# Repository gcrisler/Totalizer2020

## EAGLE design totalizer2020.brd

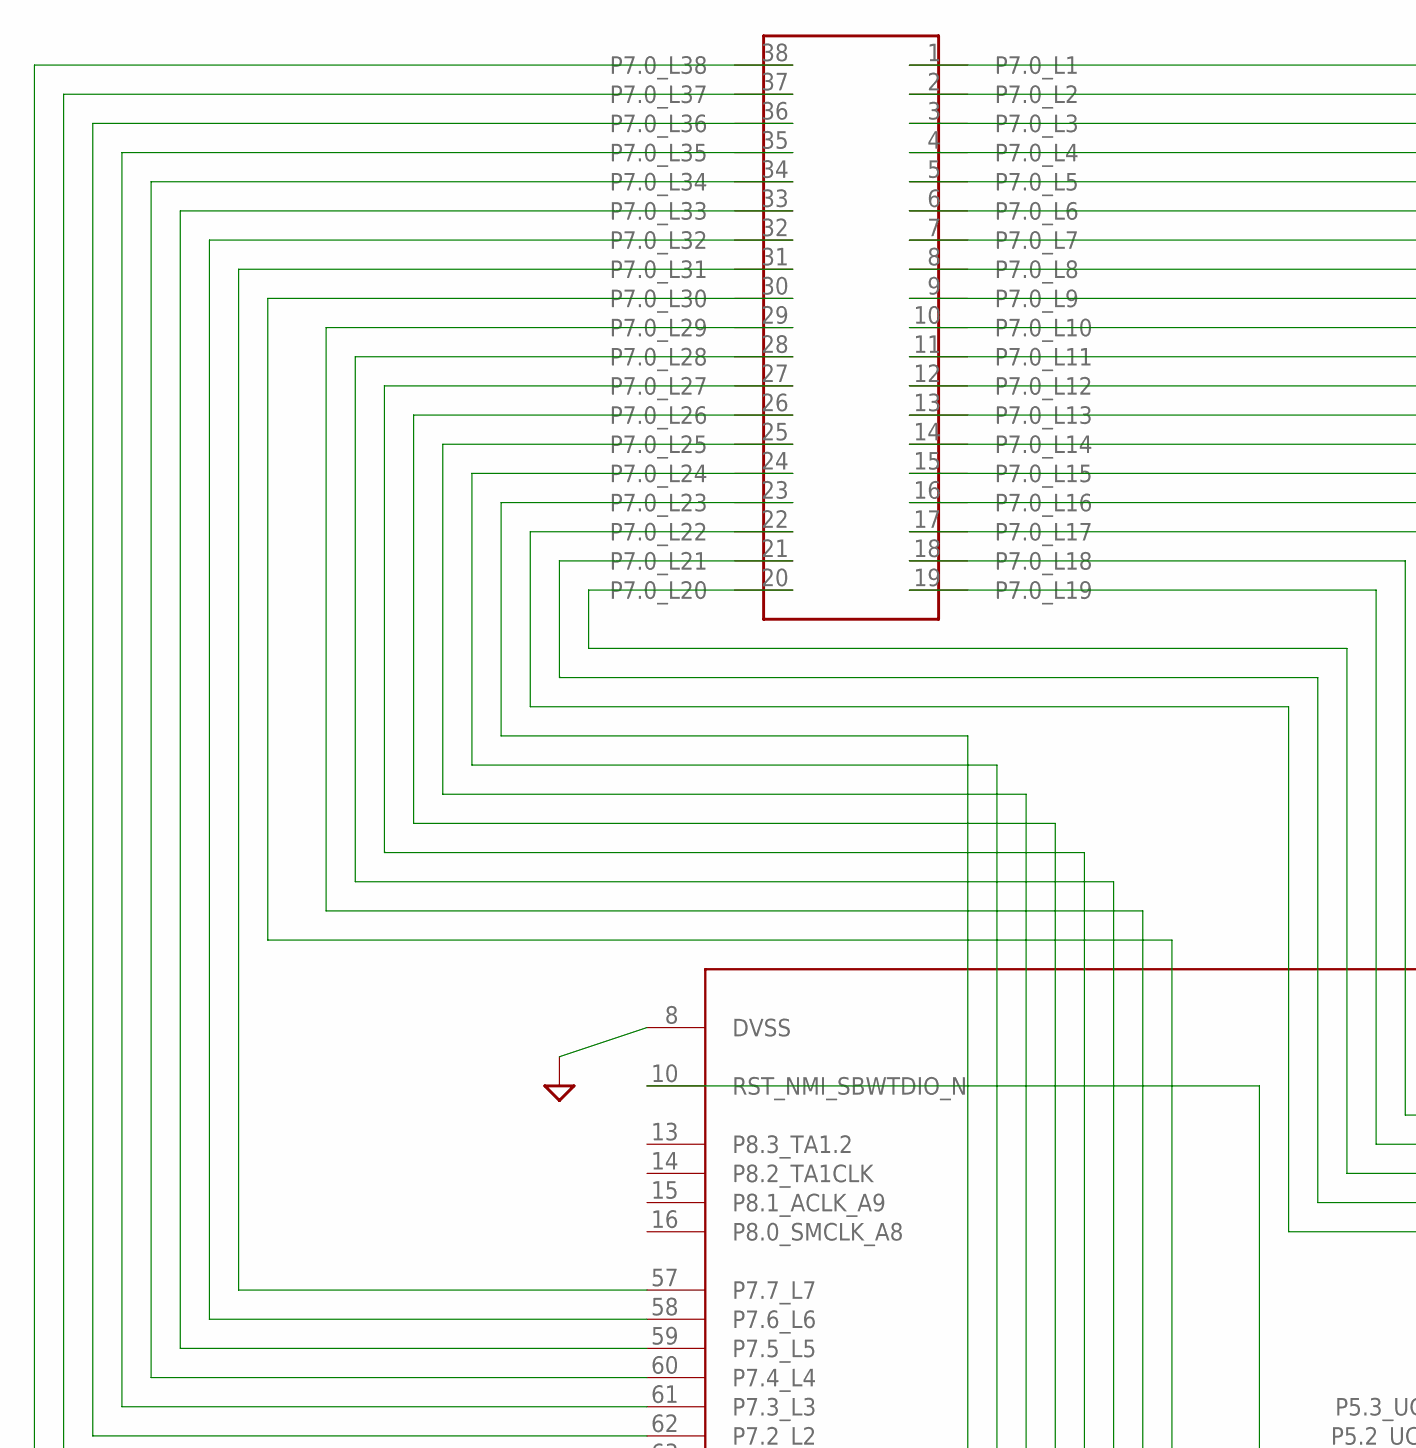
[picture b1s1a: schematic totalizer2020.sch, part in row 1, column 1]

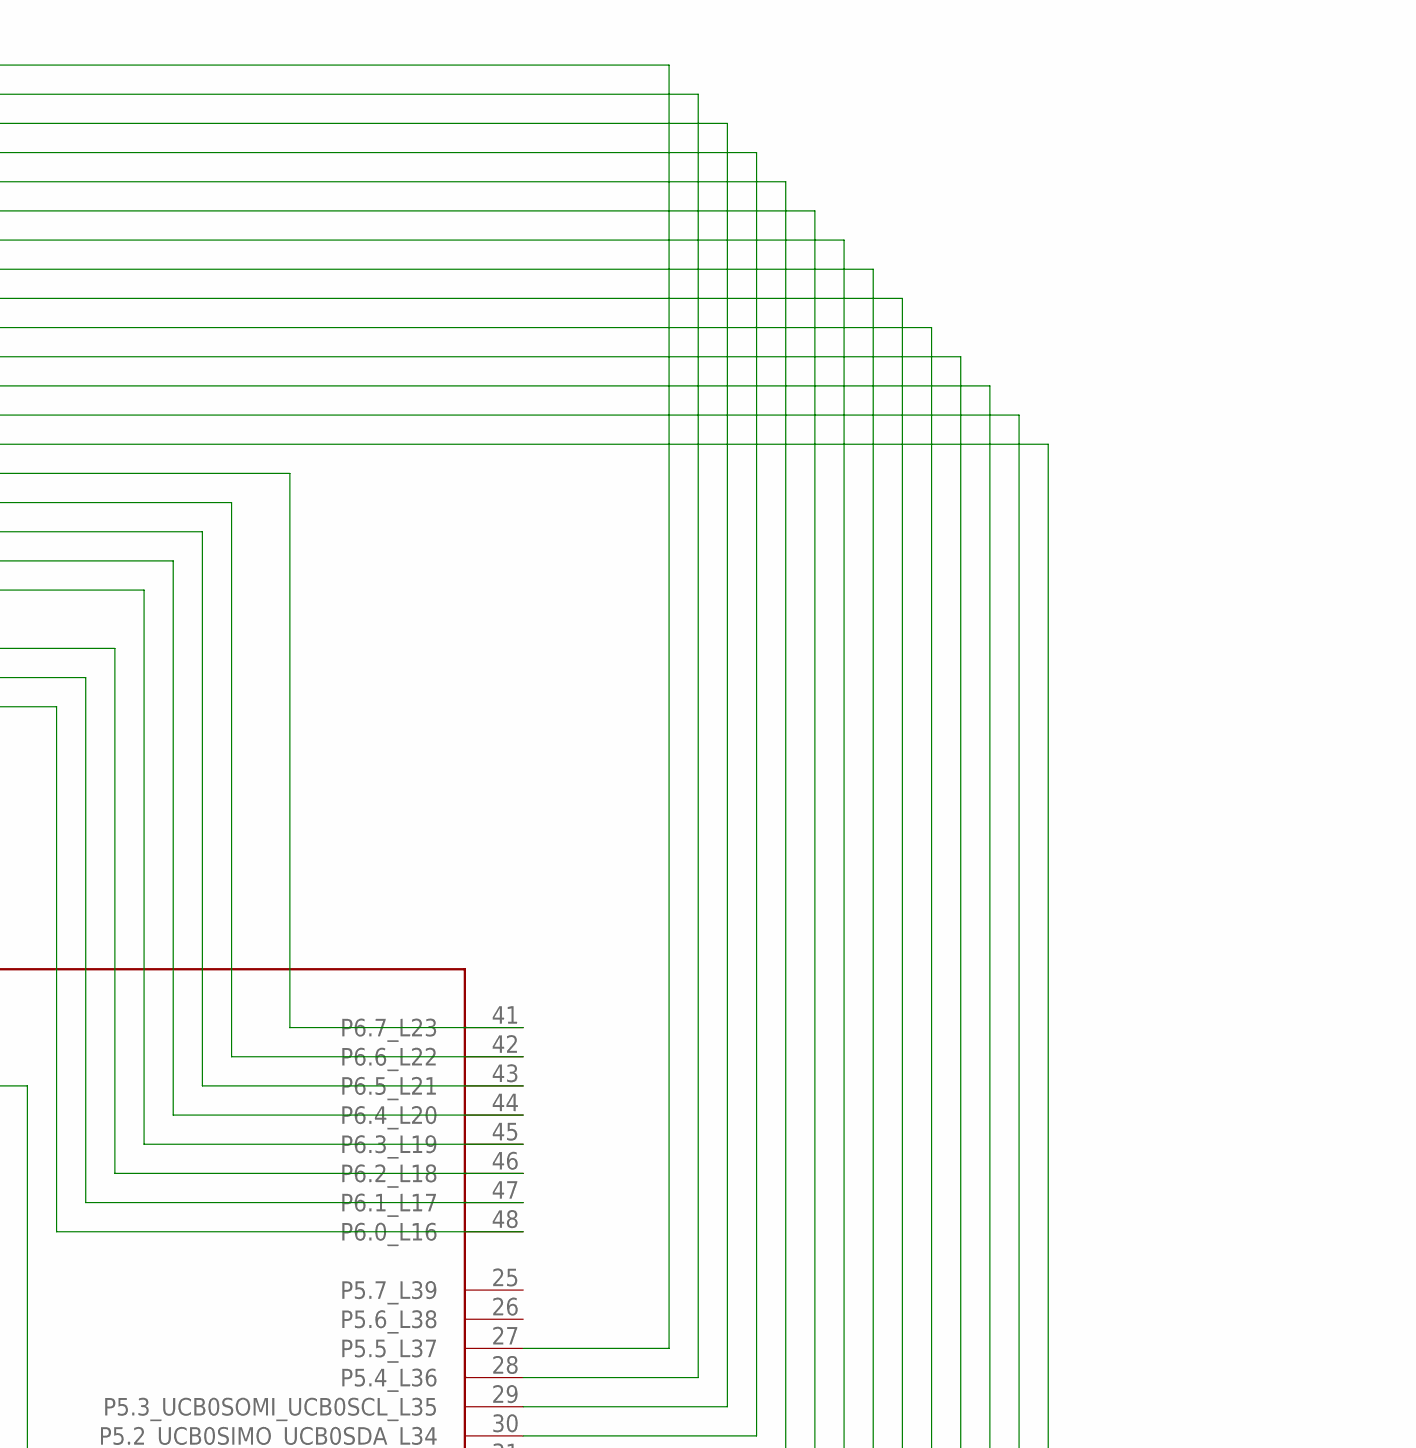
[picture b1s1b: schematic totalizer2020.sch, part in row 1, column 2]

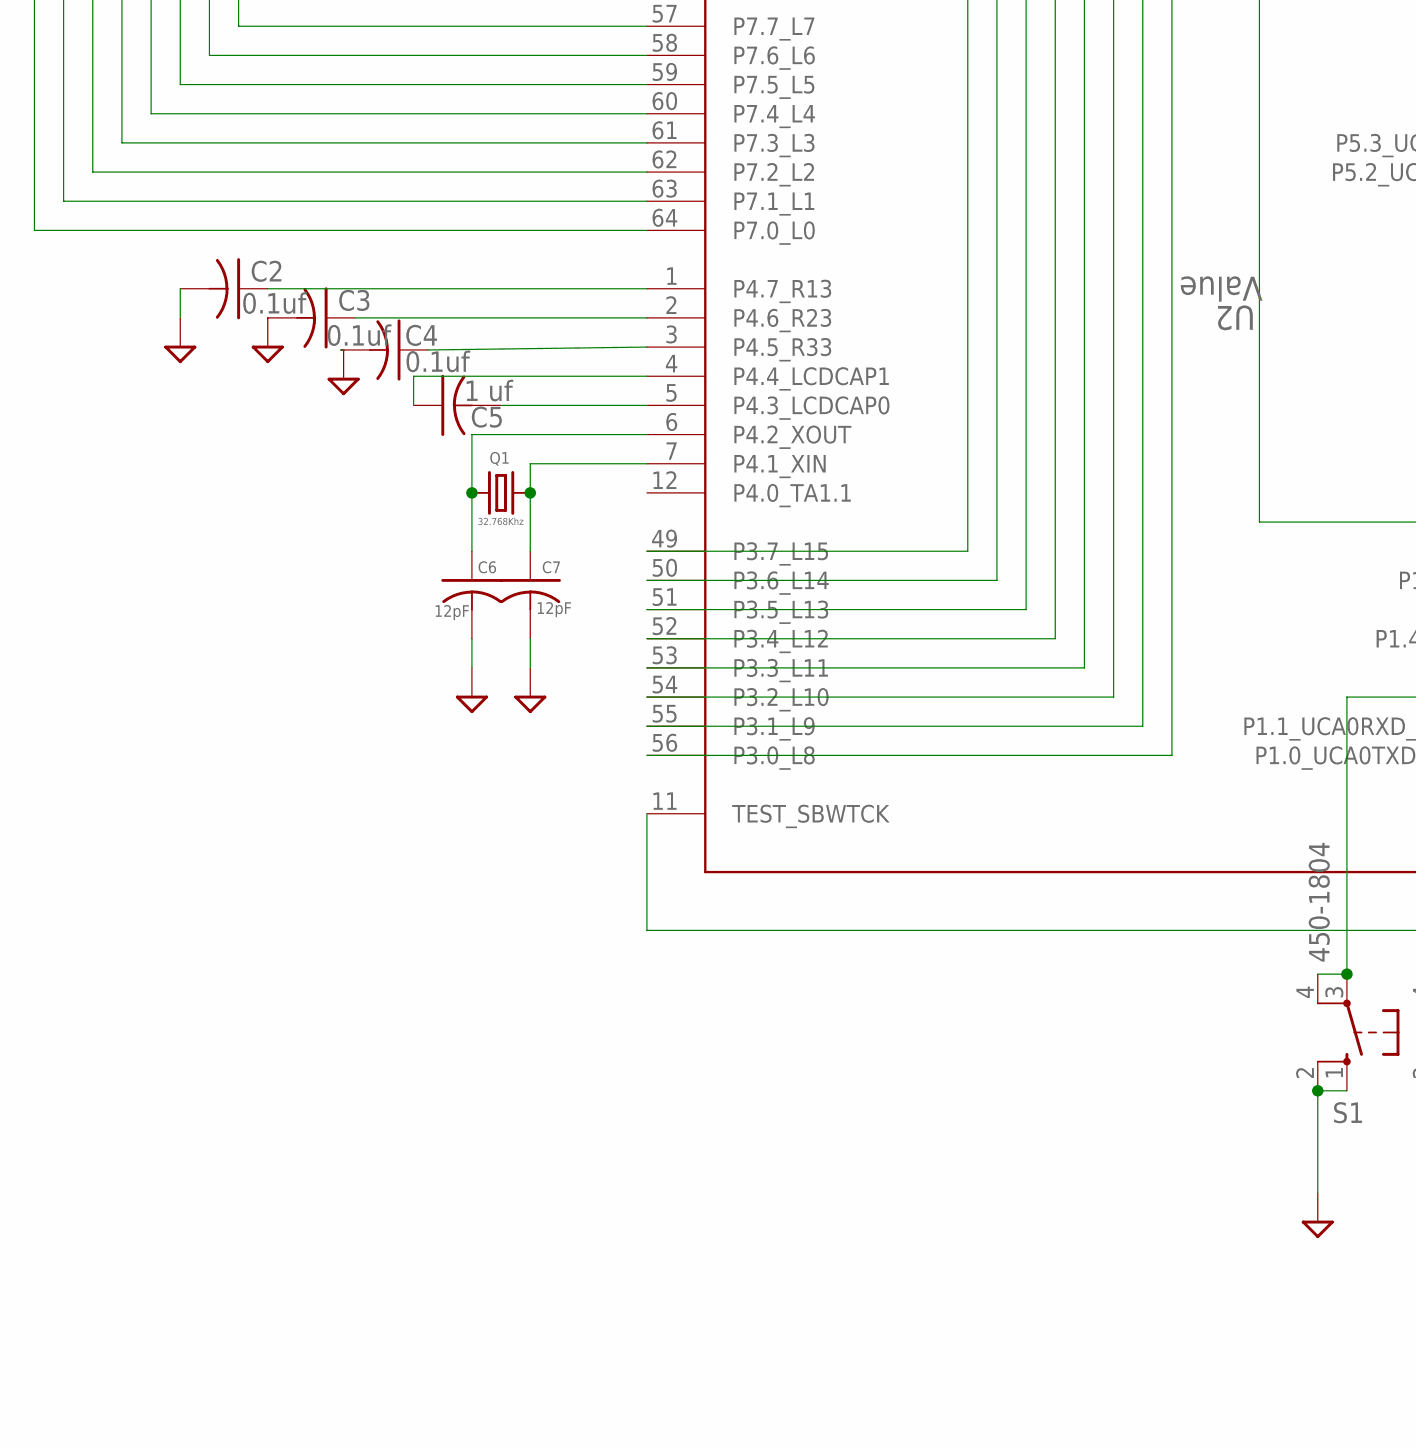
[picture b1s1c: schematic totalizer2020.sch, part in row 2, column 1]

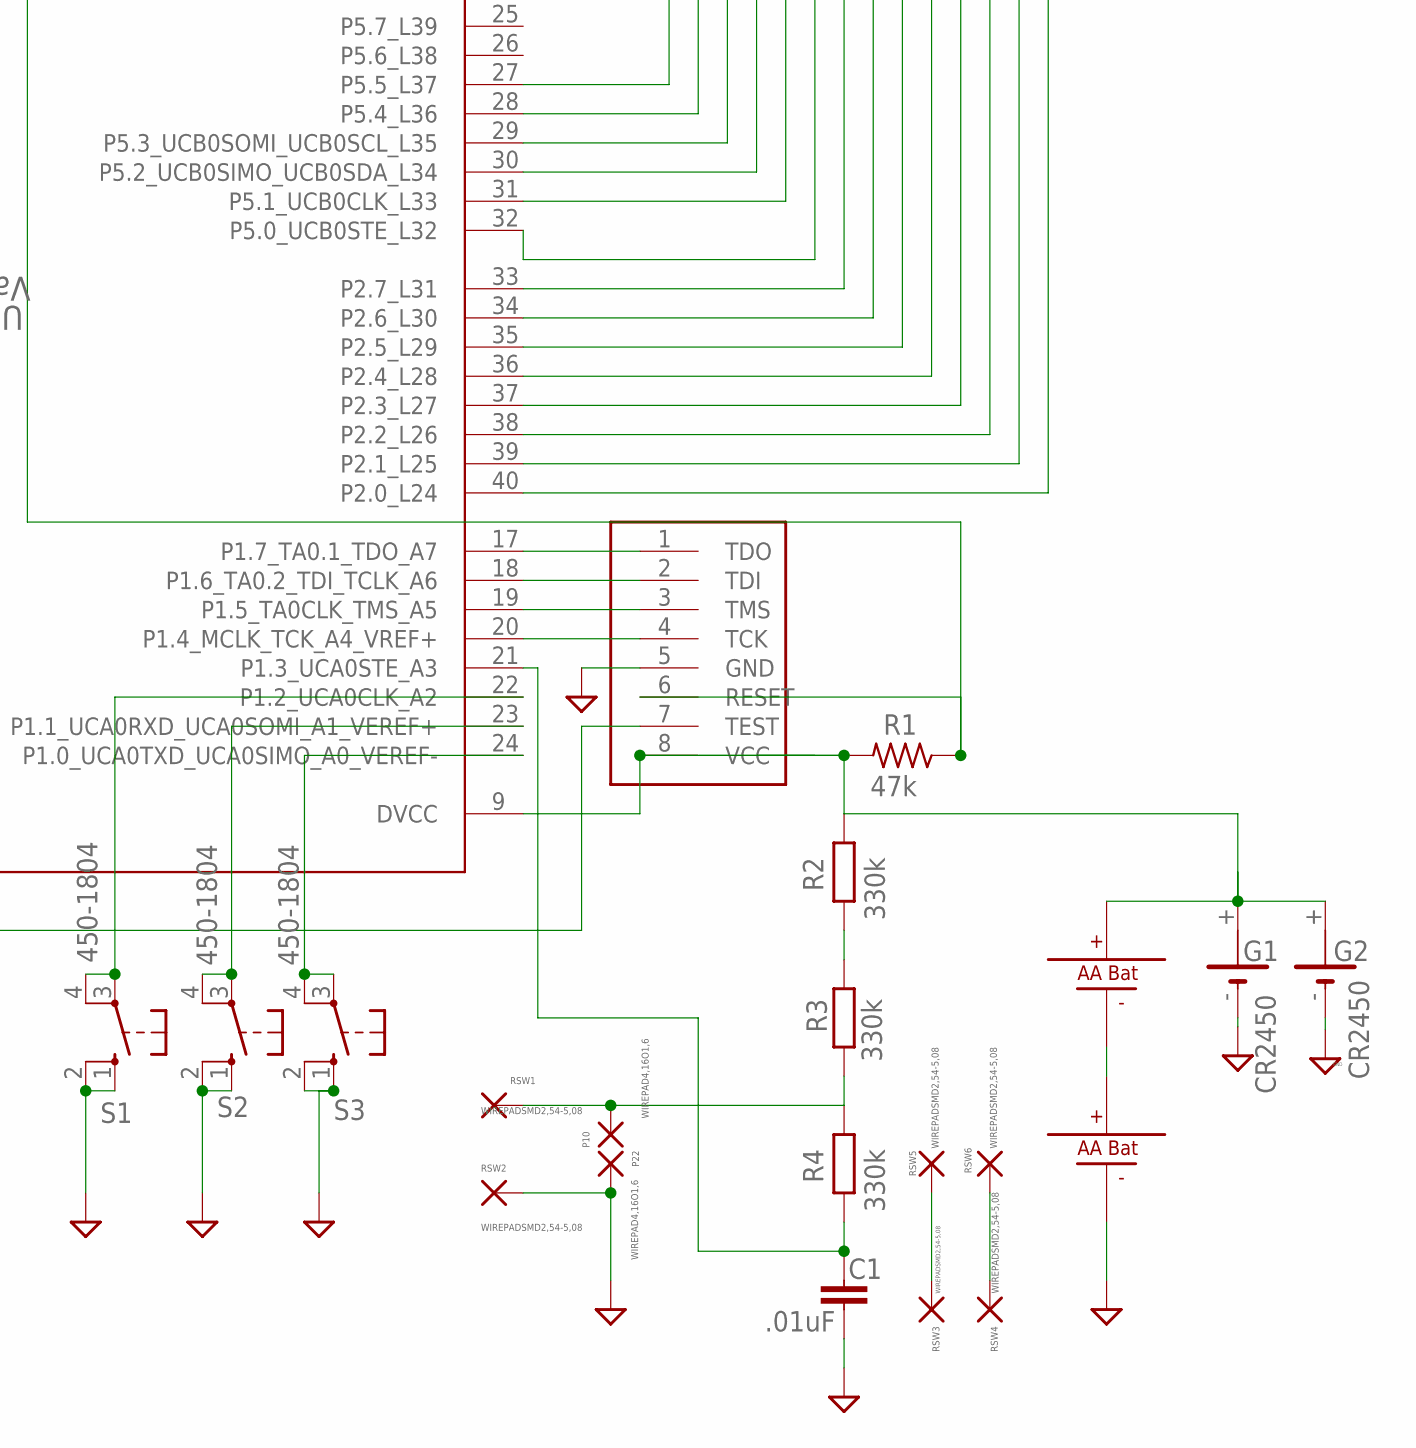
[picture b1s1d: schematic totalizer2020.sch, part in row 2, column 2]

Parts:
8PINCONNECTOR: JST-8JST-8; HDRVR8W64P150_1X8_1200X350X500B
C1: .01uF; C0805
C2, C3, C4: 0.1uf; C0805
C5: 1 uf; C0805
C6, C7: 12pF; C0805
G1, G2: CR2450; CR2430H
P10, P22: WIREPAD4,16O1,6; 4,16O1,6
Q1: 32.768Khz; 3.2X1.5
R1: 47k; R0805
R2, R3, R4: 330k; R0805
RSW1, RSW2, RSW3, RSW4, RSW5, RSW6: WIREPADSMD2,54-5,08; SMD2,54-5,08
S1, S2, S3: 450-1804; B3F-10XX
U2: Value; PM0064A_N
U$1: LCD-38LCD-38; DIP7140W53P200L5505H450Q38B
U$2, U$3: AA_BATTERY

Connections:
GND: 8PINCONNECTOR.5 (GND), C1.1, C2.2, C3.2, C4.2, C6.2, C7.2, G1.-, G2.-, P22.1, RSW2.1, S1.1 (S), S1.2 (S1), S2.1 (S), S2.2 (S1), S3.1 (S), S3.2 (S1), U2.8 (DVSS), U$3.3 (BAT_-), U$3.4 (BAT_-)
unnamed: 8PINCONNECTOR.1 (TDO), U2.17 (P1.7_TA0.1_TDO_A7)
unnamed: 8PINCONNECTOR.2 (TDI), U2.18 (P1.6_TA0.2_TDI_TCLK_A6)
unnamed: 8PINCONNECTOR.3 (TMS), U2.19 (P1.5_TA0CLK_TMS_A5)
unnamed: 8PINCONNECTOR.4 (TCK), U2.20 (P1.4_MCLK_TCK_A4_VREF+)
unnamed: C6.1, Q1.1, U2.6 (P4.2_XOUT)
unnamed: 8PINCONNECTOR.6 (RESET), R1.1, U2.10 (RST_NMI_SBWTDIO_N)
unnamed: 8PINCONNECTOR.7 (TEST), U2.11 (TEST_SBWTCK)
unnamed: RSW3.1, RSW5.1
unnamed: S2.3, S2.4 (P1), U2.23 (P1.1_UCA0RXD_UCA0SOMI_A1_VEREF+)
unnamed: S1.3, S1.4 (P1), U2.22 (P1.2_UCA0CLK_A2)
unnamed: C5.1, U2.4 (P4.4_LCDCAP1)
unnamed: S3.3, S3.4 (P1), U2.24 (P1.0_UCA0TXD_UCA0SIMO_A0_VEREF-)
unnamed: C5.2, U2.5 (P4.3_LCDCAP0)
unnamed: C4.1, U2.3 (P4.5_R33)
unnamed: C3.1, U2.2 (P4.6_R23)
unnamed: C2.1, U2.1 (P4.7_R13)
unnamed: 8PINCONNECTOR.8 (VCC), G1.+, G2.+, R1.2, R2.1, U2.9 (DVCC), U$2.2 (BAT_+), U$2.P1 (BAT_+)
unnamed: C1.2, R4.2, U2.21 (P1.3_UCA0STE_A3)
unnamed: C7.1, Q1.2, U2.7 (P4.1_XIN)
unnamed: U2.64 (P7.0_L0), U$1.38 (P7.0_L38)
unnamed: U2.63 (P7.1_L1), U$1.37 (P7.0_L37)
unnamed: U2.62 (P7.2_L2), U$1.36 (P7.0_L36)
unnamed: U2.61 (P7.3_L3), U$1.35 (P7.0_L35)
unnamed: U2.60 (P7.4_L4), U$1.34 (P7.0_L34)
unnamed: U2.59 (P7.5_L5), U$1.33 (P7.0_L33)
unnamed: U2.58 (P7.6_L6), U$1.32 (P7.0_L32)
unnamed: U2.57 (P7.7_L7), U$1.31 (P7.0_L31)
unnamed: U2.56 (P3.0_L8), U$1.30 (P7.0_L30)
unnamed: U2.55 (P3.1_L9), U$1.29 (P7.0_L29)
unnamed: U2.54 (P3.2_L10), U$1.28 (P7.0_L28)
unnamed: U2.53 (P3.3_L11), U$1.27 (P7.0_L27)
unnamed: U2.52 (P3.4_L12), U$1.26 (P7.0_L26)
unnamed: U2.51 (P3.5_L13), U$1.25 (P7.0_L25)
unnamed: U2.50 (P3.6_L14), U$1.24 (P7.0_L24)
unnamed: U2.49 (P3.7_L15), U$1.23 (P7.0_L23)
unnamed: U2.48 (P6.0_L16), U$1.22 (P7.0_L22)
unnamed: U2.47 (P6.1_L17), U$1.21 (P7.0_L21)
unnamed: U2.46 (P6.2_L18), U$1.20 (P7.0_L20)
unnamed: U2.45 (P6.3_L19), U$1.19 (P7.0_L19)
unnamed: U2.44 (P6.4_L20), U$1.18 (P7.0_L18)
unnamed: U$2.3 (BAT_-), U$2.4 (BAT_-), U$3.2 (BAT_+), U$3.P1 (BAT_+)
unnamed: U2.43 (P6.5_L21), U$1.17 (P7.0_L17)
unnamed: U2.42 (P6.6_L22), U$1.16 (P7.0_L16)
unnamed: U2.41 (P6.7_L23), U$1.15 (P7.0_L15)
unnamed: U2.40 (P2.0_L24), U$1.14 (P7.0_L14)
unnamed: U2.39 (P2.1_L25), U$1.13 (P7.0_L13)
unnamed: U2.38 (P2.2_L26), U$1.12 (P7.0_L12)
unnamed: U2.37 (P2.3_L27), U$1.11 (P7.0_L11)
unnamed: U2.36 (P2.4_L28), U$1.10 (P7.0_L10)
unnamed: U2.35 (P2.5_L29), U$1.9 (P7.0_L9)
unnamed: U2.34 (P2.6_L30), U$1.8 (P7.0_L8)
unnamed: U2.33 (P2.7_L31), U$1.7 (P7.0_L7)
unnamed: U2.32 (P5.0_UCB0STE_L32), U$1.6 (P7.0_L6)
unnamed: U2.31 (P5.1_UCB0CLK_L33), U$1.5 (P7.0_L5)
unnamed: U2.30 (P5.2_UCB0SIMO_UCB0SDA_L34), U$1.4 (P7.0_L4)
unnamed: U2.29 (P5.3_UCB0SOMI_UCB0SCL_L35), U$1.3 (P7.0_L3)
unnamed: U2.28 (P5.4_L36), U$1.2 (P7.0_L2)
unnamed: U2.27 (P5.5_L37), U$1.1 (P7.0_L1)
unnamed: RSW4.1, RSW6.1
unnamed: R2.2, R3.2
unnamed: P10.1, R3.1, R4.1, RSW1.1

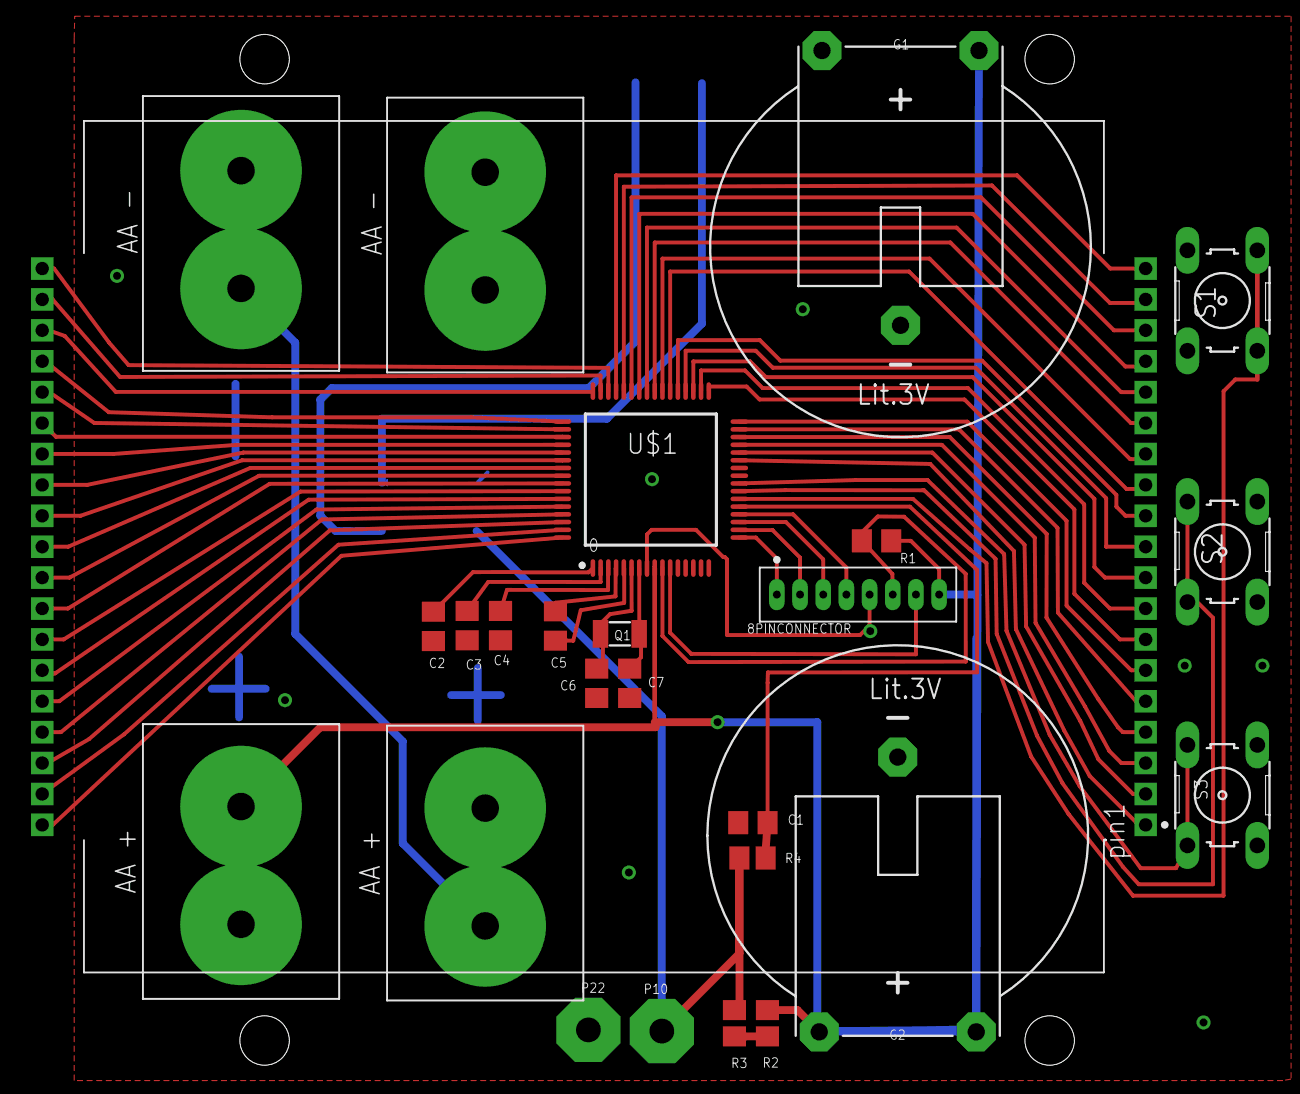
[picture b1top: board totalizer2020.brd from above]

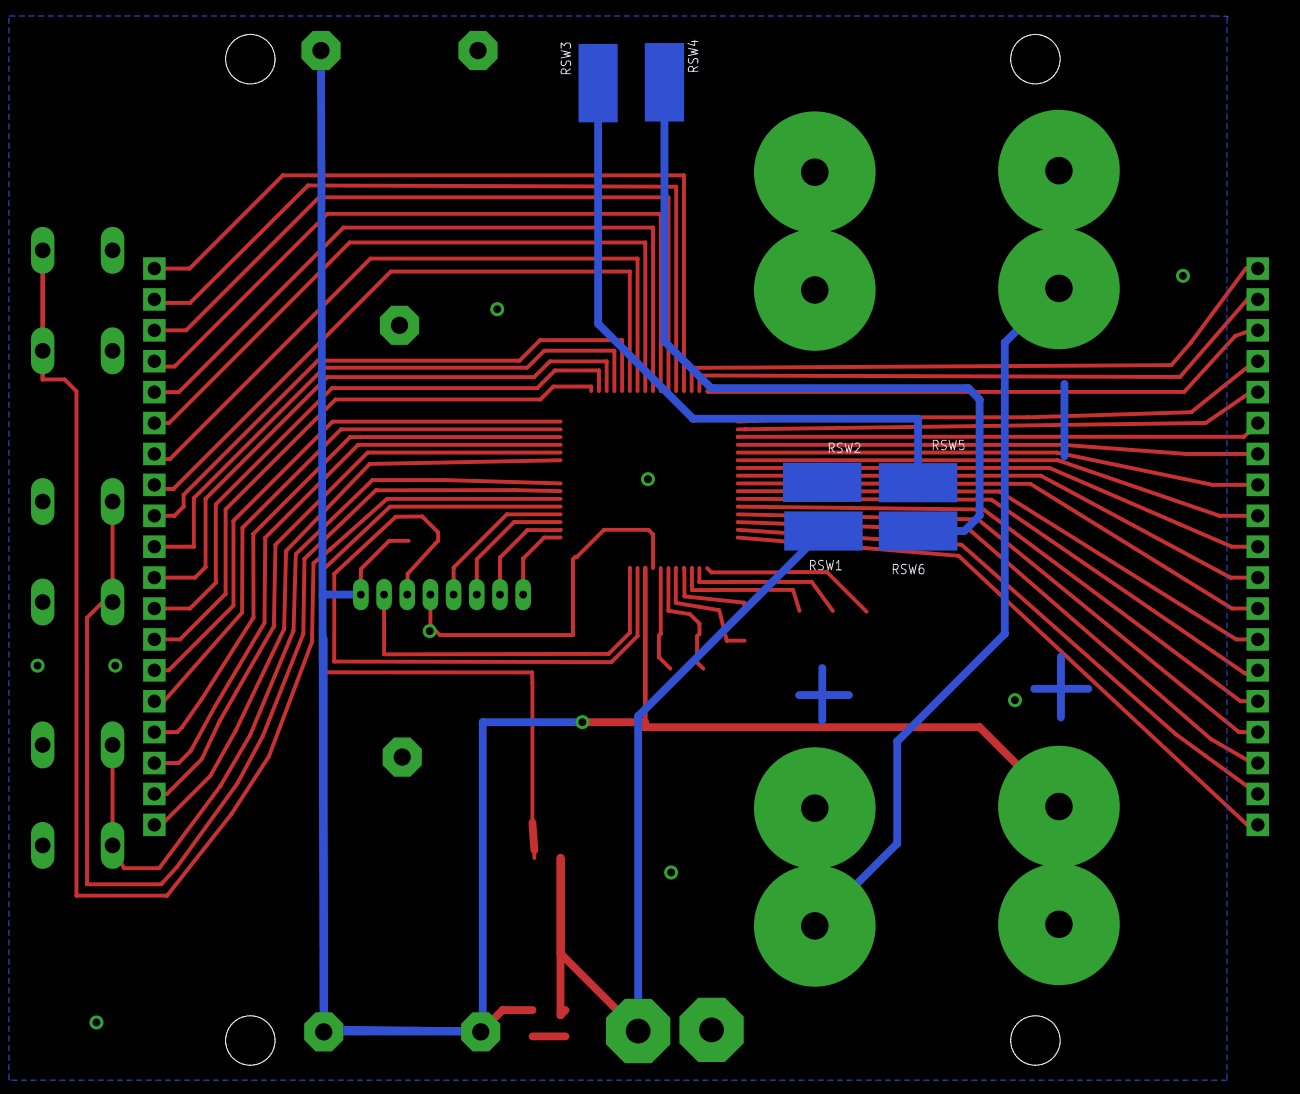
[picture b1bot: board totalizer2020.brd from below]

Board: 2 copper layers, 30 parts (6 on the bottom side), 62 nets.

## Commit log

2019-12-11 Intial commit

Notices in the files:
parts and their libraries:
crystal-geyer_V1_0: Copyright: Geyer-Electronic
